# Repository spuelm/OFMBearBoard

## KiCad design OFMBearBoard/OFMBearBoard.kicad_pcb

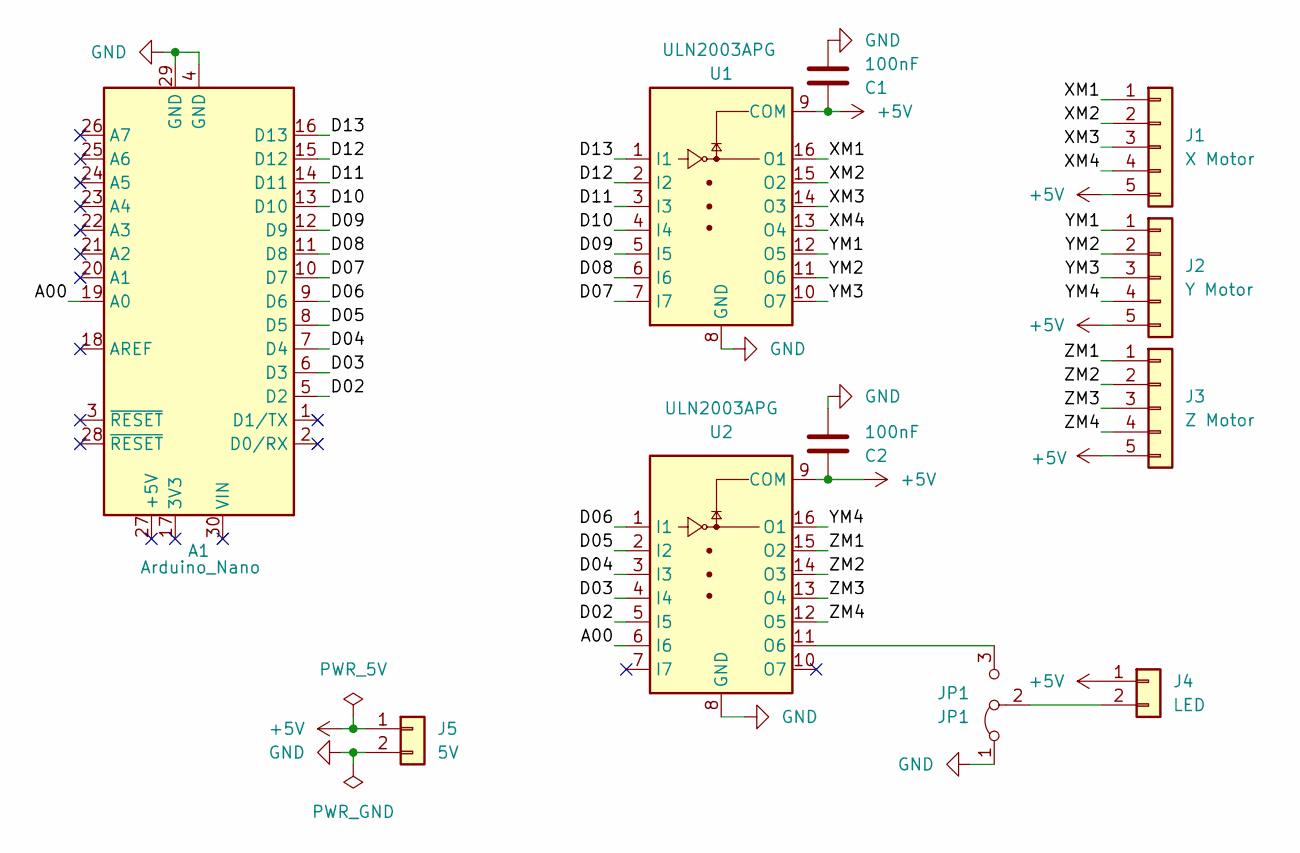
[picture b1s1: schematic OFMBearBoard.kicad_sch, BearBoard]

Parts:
A1: Arduino_Nano
C1, C2: 100nF; C_Disc_D9.0mm_W2.5mm_P5.00mm
J1: X Motor; JST_XH_B5B-XH-A_1x05_P2.50mm_Vertical
J2: Y Motor; JST_XH_B5B-XH-A_1x05_P2.50mm_Vertical
J3: Z Motor; JST_XH_B5B-XH-A_1x05_P2.50mm_Vertical
J4: LED; JST_PH_B2B-PH-K_1x02_P2.00mm_Vertical
J5: 5V; JST_PH_B2B-PH-K_1x02_P2.00mm_Vertical
JP1: JP1; PinHeader_1x03_P2.54mm_Vertical
U1, U2: ULN2003APG; DIP-16_W7.62mm_Socket

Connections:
+5V: C1.2, C2.2, J1.5, J2.5, J3.5, J4.1, J5.1, U1.9 (COM), U2.9 (COM)
/A00: A1.19 (A0), U2.6 (I6)
/D02: A1.5 (D2), U2.5 (I5)
/D03: A1.6 (D3), U2.4 (I4)
/D04: A1.7 (D4), U2.3 (I3)
/D05: A1.8 (D5), U2.2 (I2)
/D06: A1.9 (D6), U2.1 (I1)
/D07: A1.10 (D7), U1.7 (I7)
/D08: A1.11 (D8), U1.6 (I6)
/D09: A1.12 (D9), U1.5 (I5)
/D10: A1.13 (D10), U1.4 (I4)
/D11: A1.14 (D11), U1.3 (I3)
/D12: A1.15 (D12), U1.2 (I2)
/D13: A1.16 (D13), U1.1 (I1)
/XM1: J1.1, U1.16 (O1)
/XM2: J1.2, U1.15 (O2)
/XM3: J1.3, U1.14 (O3)
/XM4: J1.4, U1.13 (O4)
/YM1: J2.1, U1.12 (O5)
/YM2: J2.2, U1.11 (O6)
/YM3: J2.3, U1.10 (O7)
/YM4: J2.4, U2.16 (O1)
/ZM1: J3.1, U2.15 (O2)
/ZM2: J3.2, U2.14 (O3)
/ZM3: J3.3, U2.13 (O4)
/ZM4: J3.4, U2.12 (O5)
GND: A1.4 (GND), A1.29 (GND), C1.1, C2.1, J5.2, JP1.1 (A), U1.8 (GND), U2.8 (GND)
unnamed: J4.2, JP1.2 (C)
unnamed: JP1.3 (B), U2.11 (O6)

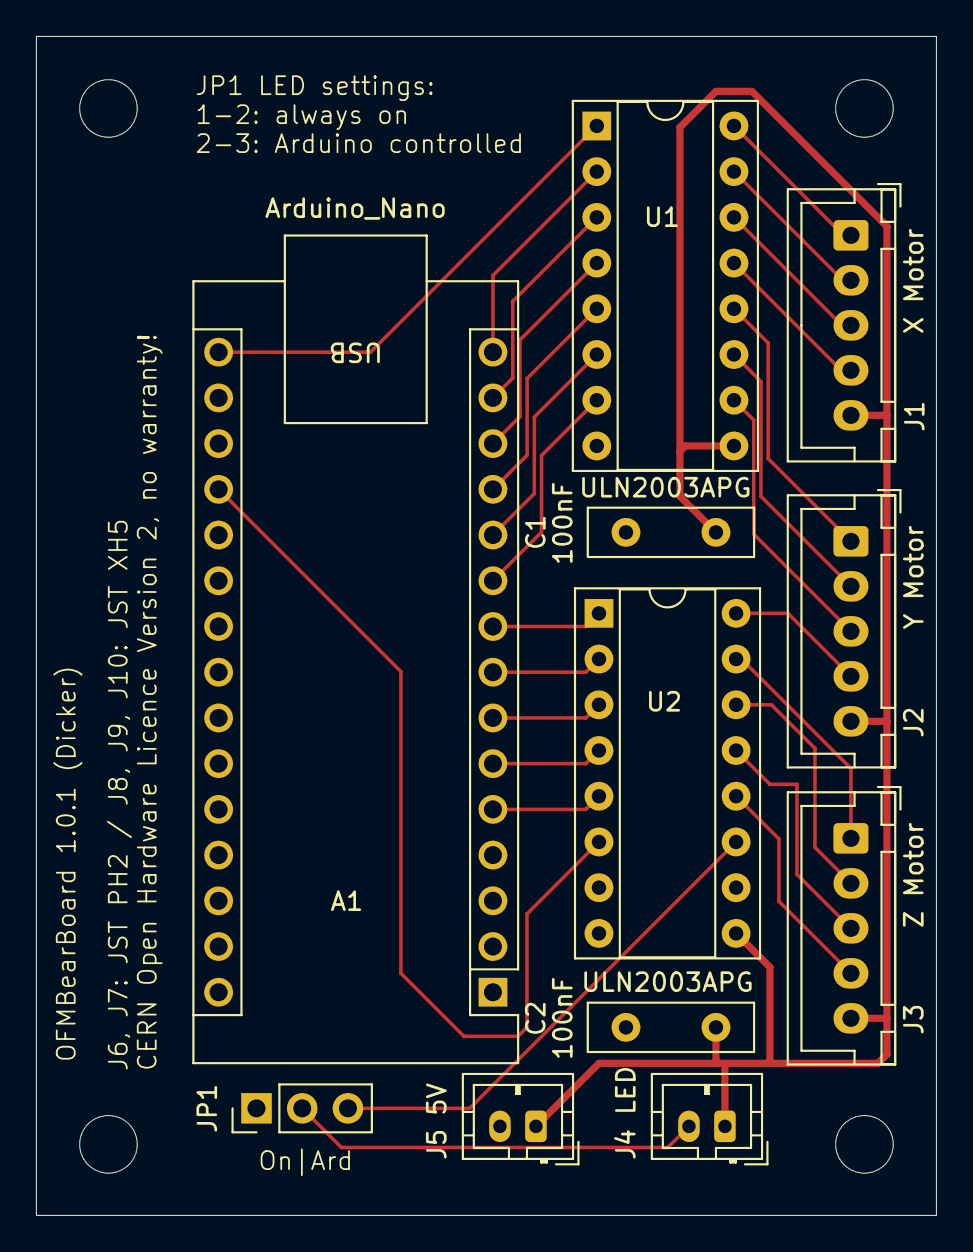
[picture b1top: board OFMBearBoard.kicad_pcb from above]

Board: 2 copper layers, 50.0 x 65.5 mm, 15 parts (0 on the bottom side), 29 nets.

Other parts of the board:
H1, H2, H3, H4: MountingHole; MountingHole_3.2mm_M3

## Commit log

2024-06-20 FIxed https://github.com/spuelm/OFMBearBoard/issues/2
    FIxed
    https://github.com/spuelm/OFMBearBoard/issues/2
    no functional impact: Typo Warranty with only one r
2024-07-03 Fixed IC aligment and capacitor size
    Fixed IC aligment and capacitor size
2024-07-15 New Gerber Zip

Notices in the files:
OFMBearBoard/OFMBearBoard.kicad_pcb:
﻿CERN Open Hardware Licence Version 2, no warranty!
